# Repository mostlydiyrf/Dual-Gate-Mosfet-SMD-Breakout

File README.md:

# Dual-Gate-Mosfet-SMD-Breakout
Breakout PCB for SOT143 dual-gate devices such as the BF998

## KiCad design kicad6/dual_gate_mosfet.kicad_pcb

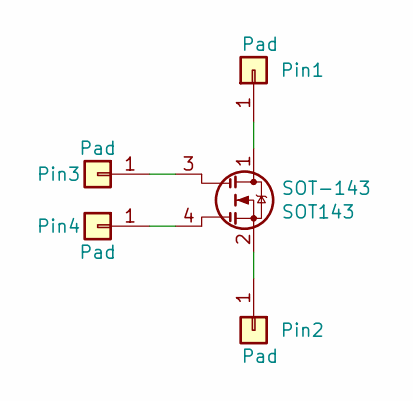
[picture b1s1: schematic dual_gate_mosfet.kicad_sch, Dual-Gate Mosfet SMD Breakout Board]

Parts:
Pin1, Pin2, Pin3, Pin4: Pad; SolderWirePad_1x01_Drill1.2mm
SOT-143: SOT143; SOT-143

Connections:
unnamed: Pin1.1, SOT-143.1 (D)
unnamed: Pin2.1, SOT-143.2 (S)
unnamed: Pin3.1, SOT-143.3 (G1)
unnamed: Pin4.1, SOT-143.4 (G2)

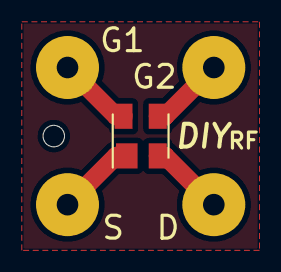
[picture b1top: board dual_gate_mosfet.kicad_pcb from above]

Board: 2 copper layers, 5 parts (0 on the bottom side), 4 nets.
